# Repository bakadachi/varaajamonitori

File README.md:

# varaajamonitori
Varaajamonitori

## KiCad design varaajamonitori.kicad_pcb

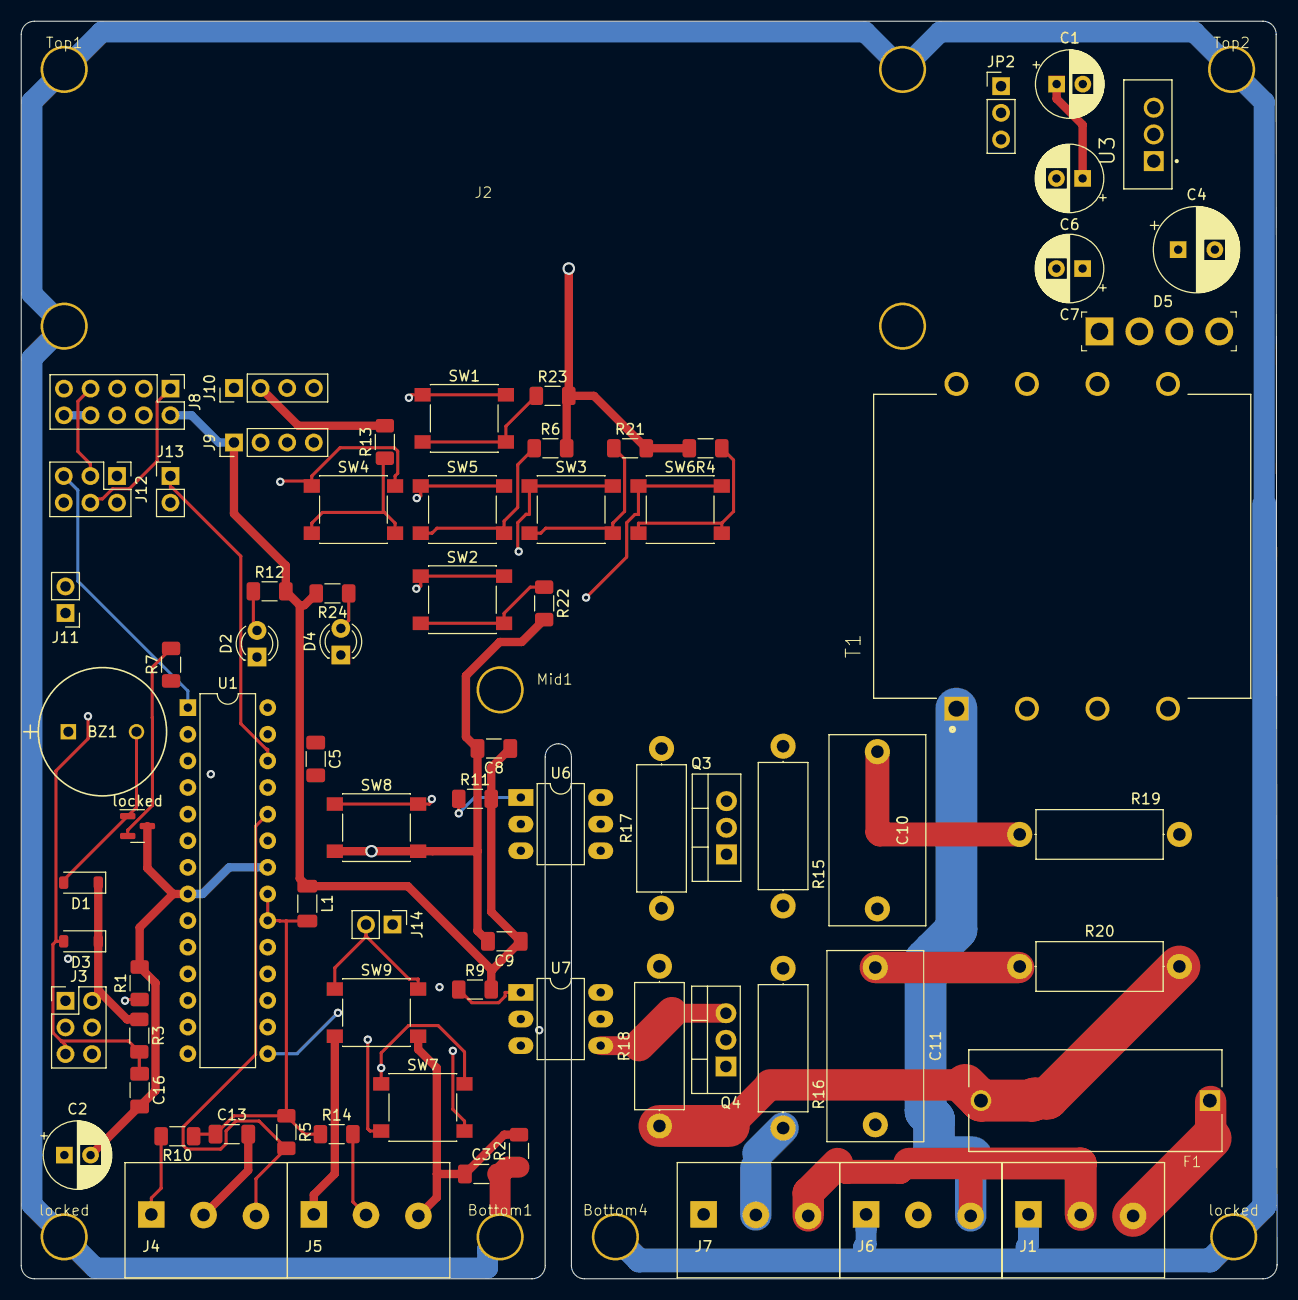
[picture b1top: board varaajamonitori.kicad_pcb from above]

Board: 4 copper layers, 119.8 x 120.0 mm, 83 parts (0 on the bottom side), 54 nets.

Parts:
BZ1: Buzzer; CEM-1206S_CUD
Bottom1, Bottom4: Conn_01x01_Pin; Drill
C1, C2: 10uf; CP_Radial_D6.3mm_P2.50mm
C3: 10nF; C_1206_3216Metric_Pad1.33x1.80mm_HandSolder
C4: 1000uF; CP_Radial_D8.0mm_P3.50mm
C5, C8, C9, C13: 100nF; C_1206_3216Metric_Pad1.33x1.80mm_HandSolder
C6, C7: 1uF; CP_Radial_D6.3mm_P2.50mm
C10, C11: 0uF22; C_Rect_L18.0mm_W9.0mm_P15.00mm_FKS3_FKP3
C16: 1uF; C_1206_3216Metric_Pad1.33x1.80mm_HandSolder
D1, D3: 1N4148W-TP; D_SOD-123
D2, D4: LED; LED_D3.0mm
D5: KBP04G; SIP-4_W3.81mm
F1: 4527; FUSE_4527
J1: 230Vin; side3poscon
J2: locked; LCD1602 RGB MOD
J3, J12: AVR-ISP-6; PinHeader_2x03_P2.54mm_Vertical
J4: SensorAAB; side3poscon
J5: SensorBCC; side3poscon
J6: RO1-230VAC-PUMP; side3poscon
J7: RO2-230VAC-PUMP; side3poscon
J8: AVR-ISP-10; PinHeader_2x05_P2.54mm_Vertical
J9, J10: Conn_01x04_Socket; PinHeader_1x04_P2.54mm_Vertical
J11, J13, J14: Conn_01x02_Socket; PinHeader_1x02_P2.54mm_Vertical
JP2: Jumper_3_Bridged12; PinHeader_1x03_P2.54mm_Vertical
L1: 10uH; L_1206_3216Metric_Pad1.22x1.90mm_HandSolder
Mid1: Conn_01x01_Pin; Drill
Q3, Q4: BT136-500; TO-220-3_Vertical
R1, R4, R6, R7, R13, R21, R22, R23: 10kR; R_1206_3216Metric_Pad1.30x1.75mm_HandSolder
R2: 1MR; R_1206_3216Metric_Pad1.30x1.75mm_HandSolder
R3: 470R; R_1206_3216Metric_Pad1.30x1.75mm_HandSolder
R5, R10, R14: 1000R; R_1206_3216Metric_Pad1.30x1.75mm_HandSolder
R9, R11: 270R; R_1206_3216Metric_Pad1.30x1.75mm_HandSolder
R12, R24: 390R; R_1206_3216Metric_Pad1.30x1.75mm_HandSolder
R15, R16: 63R; R_Axial_DIN0414_L11.9mm_D4.5mm_P15.24mm_Horizontal
R17, R18, R19, R20: 47R; R_Axial_DIN0414_L11.9mm_D4.5mm_P15.24mm_Horizontal
SW1: UpSw; SW_Push_1P1T_NO_6x6mm_H9.5mm
SW2: DwnSw; SW_Push_1P1T_NO_6x6mm_H9.5mm
SW3: RightSw; SW_Push_1P1T_NO_6x6mm_H9.5mm
SW4: LeftSw; SW_Push_1P1T_NO_6x6mm_H9.5mm
SW5: SelSw; SW_Push_1P1T_NO_6x6mm_H9.5mm
SW6: RetSw; SW_Push_1P1T_NO_6x6mm_H9.5mm
SW7: Reset; SW_Push_1P1T_NO_6x6mm_H9.5mm
SW8: Test1; SW_Push_1P1T_NO_6x6mm_H9.5mm
SW9: Test2; SW_Push_1P1T_NO_6x6mm_H9.5mm
T1: FS12-090-C2; XFMR_FS12-090-C2
Top1, Top2: Conn_01x01_Pin; Drill
U1: ATmega328P-P; DIP-28_W7.62mm
U3: L7805CV; TO255P1040X460X1968-3
U6, U7: MOC3020M; DIP-6_W7.62mm_LongPads
locked: Conn_01x01_Pin; Drill
locked#2: Conn_01x01_Pin; Drill
locked#3: NPN; SOT-23

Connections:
+5V: C1.1, C6.1, C7.1, JP2.1 (A), U3.3 (OUTPUT)
/0-wire: F1.1, J1.3
/5V1DIRTY: C4.1, D5.1 (+), U3.1 (INPUT)
/ACT: T1.2, T1.3
/AVCC: C13.1, L1.2, R5.1, R10.1, R14.1, U1.20 (AVCC), U1.21 (AREF)
/DwnSw: SW2.1, U1.15 (PB1)
/LeftSw: SW4.1, U1.11 (PD5)
/M1A: R17.2, U6.6
/M1B: Q3.3 (G), R15.2, U6.4
/M2A: R18.2, U7.6
/M2B: Q4.3 (G), R16.2, U7.4
/MISO: J3.1 (MISO), J8.9 (MISO), J12.1 (MISO), U1.18 (PB4)
/MOSI: J3.4 (MOSI), J8.1 (MOSI), J12.4 (MOSI), U1.17 (PB3)
/RX: D4.1 (K), J11.2, U1.2 (PD0)
/RetSw: SW6.1, U1.13 (PD7)
/RightSw: SW3.1, U1.16 (PB2)
/SCK: J3.3 (SCK), J8.7 (SCK), J12.3 (SCK), U1.19 (PB5)
/SCL: J9.3, J10.3, U1.28 (PC5)
/SDA: J9.4, J10.4, U1.27 (PC4)
/SELA: J13.1, U1.26 (PC3)
/SELB: J13.2, U1.6 (PD4)
/SelSw: SW5.1, U1.12 (PD6)
/TRIAC AC M1: C10.2, J6.2, Q3.1 (A1), R15.1
/TRIAC AC M2: C11.2, J7.2, Q4.1 (A1), R16.1
/TX: D2.1 (K), J11.1, U1.3 (PD1)
/UpSw: SW1.1, U1.14 (PB0)
/driver-M1: J14.1, SW8.1, U1.4 (PD2), U6.2
/driver-M2: J14.2, SW9.1, U1.5 (PD3), U7.2
/sensor1: J4.1, R10.2, U1.23 (PC0)
/sensor2: J4.3, R5.2, U1.24 (PC1)
/sensor3: J5.2, R14.2, U1.25 (PC2)
/~RESET: C16.1, D3.2 (A), J3.5 (~RST), J8.5 (~RST), J12.5 (~RST), R3.2, SW7.1, U1.1 (~RESET/PC6)
AC: F1.2, Q3.2 (A2), Q4.2 (A2), R17.1, R18.1, R19.2, R20.2, T1.4
Earth_Protective: Bottom1.1, Bottom4.1, C3.2, J1.1, J2.1, J6.1, J7.1, Mid1.1, R2.1, Top1.1, Top2.1, locked.1, locked#2.1
GND: C1.2, C2.2, C3.1, C4.2, C6.2, C7.2, C8.2, C9.2, C13.2, C16.2, D5.4 (-), J3.6 (GND), J4.2, J5.1, J5.3, J8.4 (GND), J8.6 (GND), J8.8 (GND), J8.10 (GND), J9.2, J10.2, J12.6 (GND), R1.2, R2.2, R4.2, R6.2, R13.2, R21.2, R22.2, R23.2, SW8.2, SW9.2, U1.8 (GND), U1.22 (GND), U3.2 (GROUND), locked#3.3 (E)
GNDREF: J1.2, J6.3, J7.3, T1.1
unnamed: BZ1.2 (+), D1.2 (A), locked#3.1 (C)
unnamed: C10.1, R19.1
unnamed: C11.1, R20.1
unnamed: D2.2 (A), R12.1
unnamed: D4.2 (A), R24.1
unnamed: D5.2 (AC), T1.5, T1.7
unnamed: D5.3 (AC), T1.6, T1.8
unnamed: R7.2, locked#3.2 (B)
unnamed: R1.1, SW7.2
unnamed: R4.1, SW6.2
unnamed: R6.1, SW5.2
unnamed: R9.1, U7.1
unnamed: R11.1, U6.1
unnamed: R13.1, SW4.2
unnamed: R21.1, SW3.2
unnamed: R22.1, SW2.2
unnamed: R23.1, SW1.2
VDD: BZ1.1 (-), C2.1, C8.1, C9.1, D1.1 (K), D3.1 (K), J3.2 (VCC), J8.2 (VCC), J9.1, J10.1, J12.2 (VCC), JP2.2 (C), L1.1, R3.1, R9.2, R11.2, R12.2, R24.2, U1.7 (VCC)

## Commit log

2024-11-13 Fixed regulator footprints, removed AC switch
2024-11-14 Big bug fix to TRIAC
2024-11-15 Changing AC, edge, ACDC
2024-11-15 New routing tests
2024-11-19 Adding ISP, UART, I2C plus commenting
2025-02-18 some changes
